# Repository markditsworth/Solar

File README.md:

# Solar

#### 300 Watt Solar Bank with Battery Storage

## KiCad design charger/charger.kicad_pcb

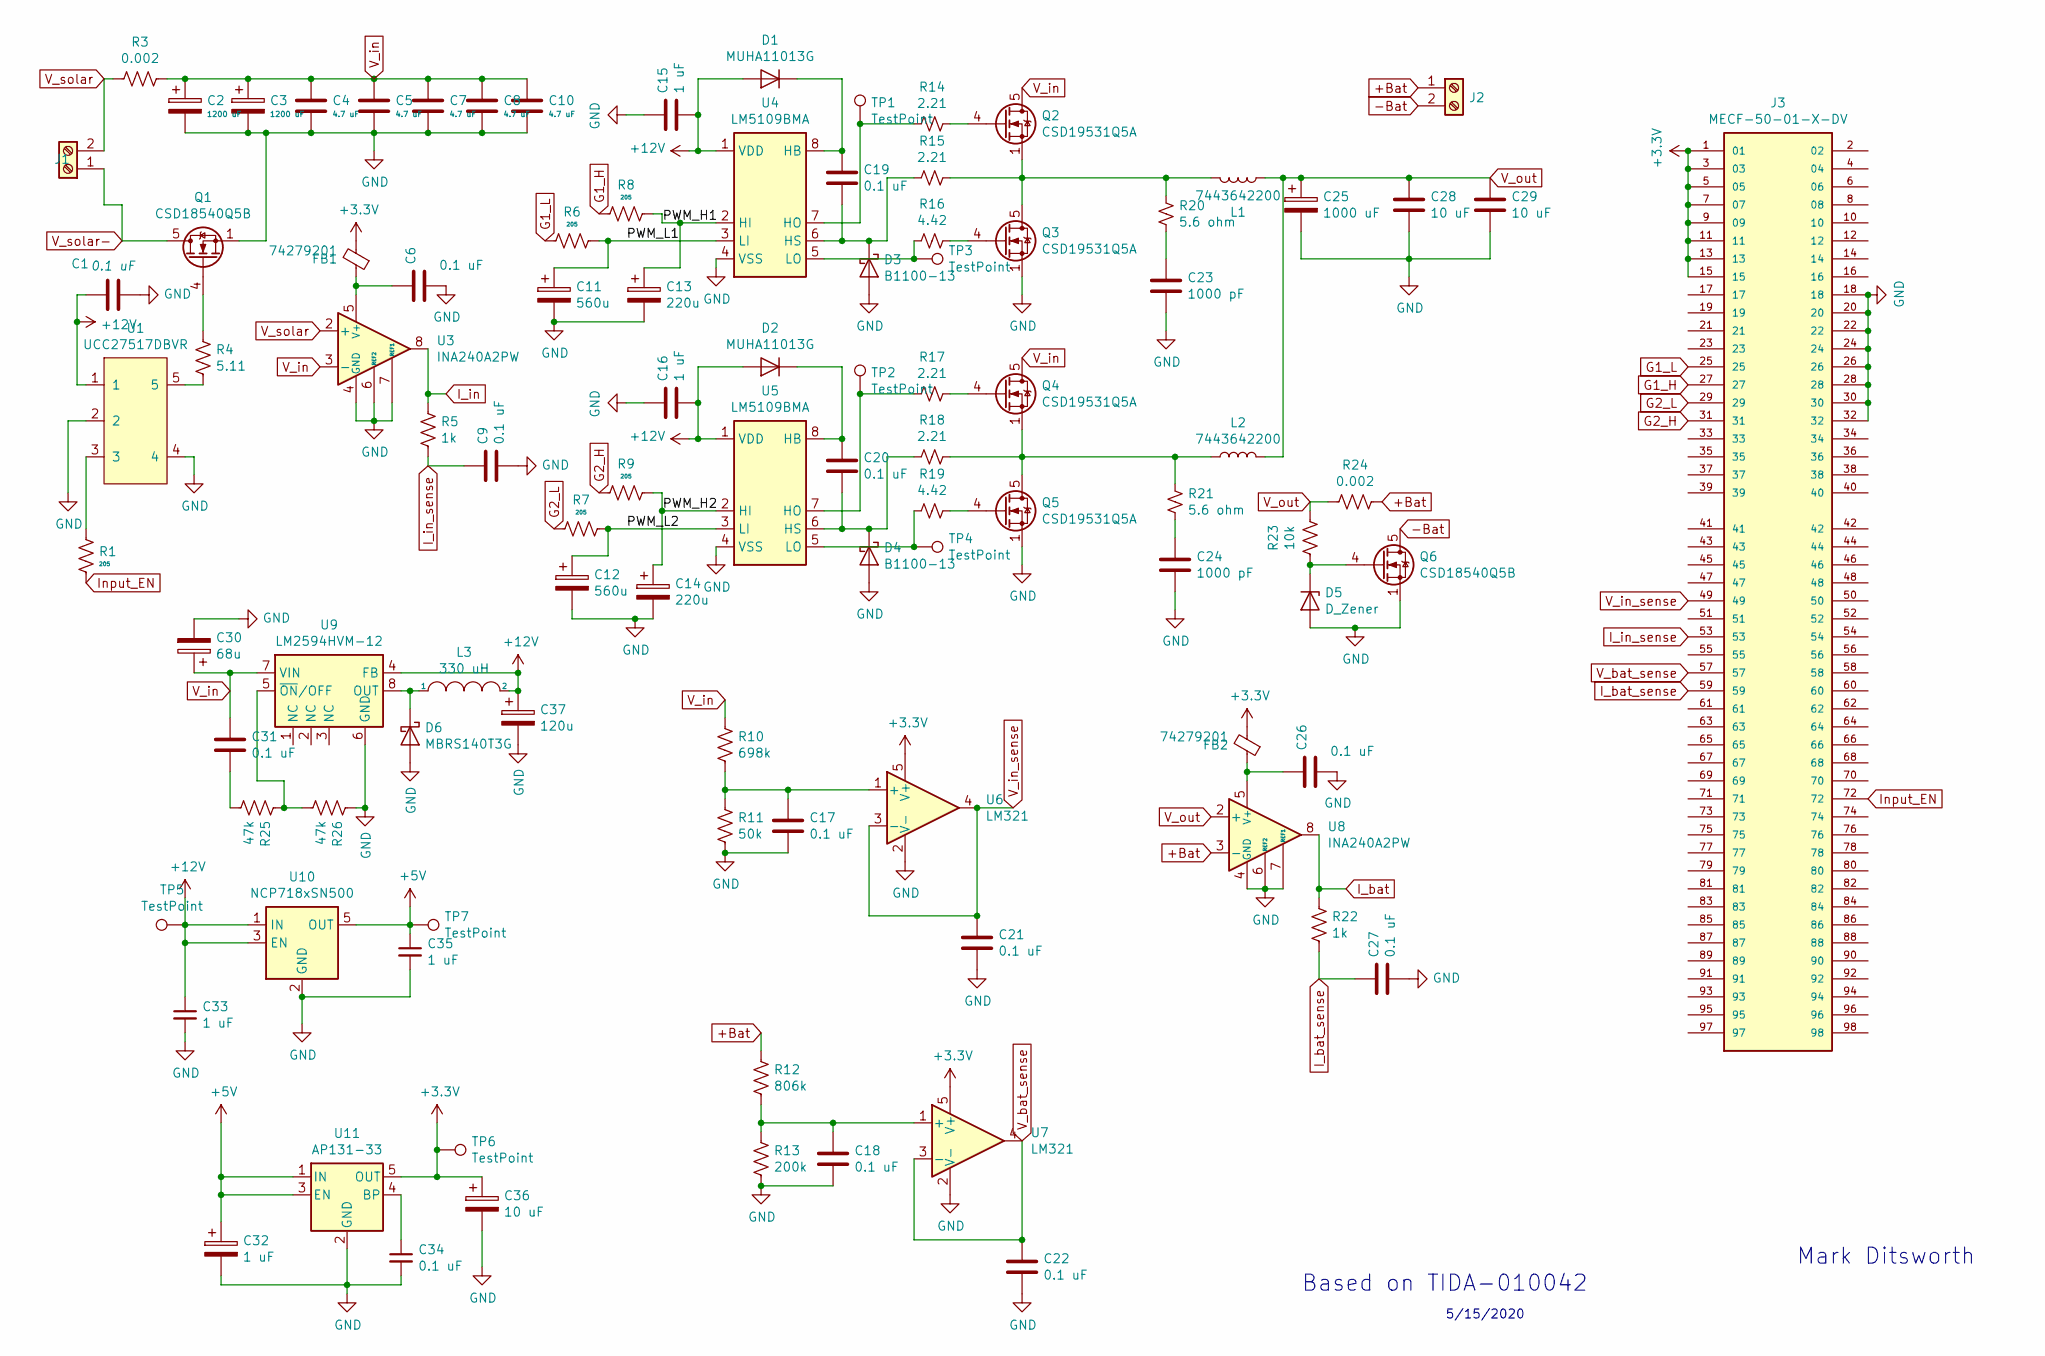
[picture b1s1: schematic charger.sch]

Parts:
C1, C6, C9, C17, C18, C19, C20, C21, C22, C26, C27, C31, C34: 0.1 uF; C_1206_3216Metric
C2, C3: 1200 uF; CP_Radial_D25.0mm_P10.00mm_SnapIn
C4, C5, C7, C8, C10: 4.7 uF; C_1206_3216Metric
C11, C12: 560u; C_Elec_8x10.2
C13, C14: 220u; C_Elec_6.3x7.7
C15, C16, C33, C35: 1 uF; C_1206_3216Metric
C23, C24: 1000 pF; C_1206_3216Metric
C25: 1000 uF; CP_Radial_D30.0mm_P10.00mm_SnapIn
C28, C29: 10 uF; C_1206_3216Metric
C30: 68u; C_Elec_8x10.2
C32: 1 uF; CP_Radial_D5.0mm_P2.00mm
C36: 10 uF; CP_Radial_D6.3mm_P2.50mm
C37: 120u; C_Elec_10x10.2
D1, D2: MUHA11013G; D_SMA
D3, D4: B1100-13; D_SMA
D5: D_Zener; D_SMA
D6: MBRS140T3G; D_SMB_Handsoldering
FB1, FB2: 74279201; L_0805_2012Metric
J1, J2: OSTT7020150; Phoenix_MKDS_6.35
J3: MECF-50-01-X-DV; SAMTEC_MECF-50-01-X-DV; PARTREV D
L1, L2: 7443642200; 7443642200 _Inductor
L3: 330 uH; L_Bourns_SRR1260
Q1, Q6: CSD18540Q5B; TDSON-8-1
Q2, Q3, Q4, Q5: CSD19531Q5A; TDSON-8-1
R1, R6, R7, R8, R9: 205; R_1206_3216Metric
R3, R24: 0.002; R_2512_6332Metric
R4: 5.11; R_1206_3216Metric
R5, R22: 1k; R_1206_3216Metric
R10: 698k; R_1206_3216Metric
R11: 50k; R_1206_3216Metric
R12: 806k; R_1206_3216Metric
R13: 200k; R_1206_3216Metric
R14, R15, R17, R18: 2.21; R_1206_3216Metric
R16, R19: 4.42; R_1206_3216Metric
R20, R21: 5.6 ohm; R_1206_3216Metric
R23: 10k; R_1206_3216Metric
R25, R26: 47k; R_1206_3216Metric
TP1, TP2, TP3, TP4, TP5, TP6, TP7: TestPoint; Pin_D1.4mm_L8.5mm_W2.8mm_FlatFork
U1: UCC27517DBVR; SOT-23-5
U3, U8: INA240A2PW; SOIC-8_3.9x4.9mm_P1.27mm
U4, U5: LM5109BMA; SOIC-8_3.9x4.9mm_P1.27mm
U6, U7: LM321; SOT-23-5
U9: LM2594HVM-12; SOIC-8_3.9x4.9mm_P1.27mm
U10: NCP718xSN500; SOT-23-5
U11: AP131-33; SOT-23-5

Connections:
+3V3: C36.1, FB1.2, FB2.2, J3.1, J3.3, J3.5, J3.7, J3.9, J3.11, J3.13, J3.15, TP6.1, U6.5 (V+), U7.5 (V+), U11.5 (OUT)
+5V: C32.1, C35.1, TP7.1, U10.5 (OUT), U11.1 (IN), U11.3 (EN)
+12V: C1.2, C15.2, C16.2, C33.1, C37.1, D1.2 (A), D2.2 (A), L3.2, TP5.1, U1.1, U4.1 (VDD), U5.1 (VDD), U9.4 (FB), U10.1 (IN), U10.3 (EN)
+Bat: J2.1, R12.1, R24.1, U8.3 (-)
-Bat: J2.2, Q6.5 (D)
/PWM_H1: C13.1, R8.1, U4.2 (HI)
/PWM_H2: C14.1, R9.1, U5.2 (HI)
/PWM_L1: C11.1, R6.1, U4.3 (LI)
/PWM_L2: C12.1, R7.1, U5.3 (LI)
G1_H: J3.27, R8.2
G1_L: J3.25, R6.2
G2_H: J3.31, R9.2
G2_L: J3.29, R7.2
GND: C1.1, C2.2, C3.2, C4.2, C5.2, C6.2, C7.2, C8.2, C9.2, C10.2, C11.2, C12.2, C13.2, C14.2, C15.1, C16.1, C17.2, C18.2, C21.2, C22.2, C23.2, C24.2, C25.2, C26.2, C27.2, C28.2, C29.2, C30.2, C32.2, C33.2, C34.2, C35.2, C36.2, C37.2, D3.2 (A), D4.2 (A), D5.2 (A), D6.2 (A), J3.18, J3.20, J3.22, J3.24, J3.26, J3.28, J3.30, J3.32, Q1.1 (S), Q1.2 (S), Q1.3 (S), Q3.1 (S), Q3.2 (S), Q3.3 (S), Q5.1 (S), Q5.2 (S), Q5.3 (S), Q6.1 (S), Q6.2 (S), Q6.3 (S), R11.2, R13.2, R26.1, U1.2, U1.4, U3.1 (GND), U3.4 (GND), U3.6 (REF2), U3.7 (REF1), U4.4 (VSS), U5.4 (VSS), U6.2 (V-), U7.2 (V-), U8.1 (GND), U8.4 (GND), U8.6 (REF2), U8.7 (REF1), U9.6 (GND), U10.2 (GND), U11.2 (GND)
I_bat: R22.1, U8.8
I_bat_sense: C27.1, J3.59, R22.2
I_in: R5.1, U3.8
I_in_sense: C9.1, J3.53, R5.2
Input_EN: J3.72, R1.1
unnamed: C6.1, FB1.1, U3.5 (V+)
unnamed: C17.1, R10.2, R11.1, U6.1 (+)
unnamed: C18.1, R12.2, R13.1, U7.1 (+)
unnamed: C19.1, D1.1 (K), U4.8 (HB)
unnamed: C19.2, D3.1 (K), R15.2, U4.6 (HS)
unnamed: C20.1, D2.1 (K), U5.8 (HB)
unnamed: C20.2, D4.1 (K), R18.2, U5.6 (HS)
unnamed: C23.1, R20.2
unnamed: C24.1, R21.2
unnamed: C26.1, FB2.1, U8.5 (V+)
unnamed: C31.2, R25.2
unnamed: C34.1, U11.4 (BP)
unnamed: D5.1 (K), Q6.4 (G), R23.2
unnamed: D6.1 (K), L3.1, U9.8 (OUT)
unnamed: L1.2, Q2.1 (S), Q2.2 (S), Q2.3 (S), Q3.5 (D), R15.1, R20.1
unnamed: L2.1, Q4.1 (S), Q4.2 (S), Q4.3 (S), Q5.5 (D), R18.1, R21.1
unnamed: Q1.4 (G), R4.1
unnamed: Q2.4 (G), R14.1
unnamed: Q3.4 (G), R16.1
unnamed: Q4.4 (G), R17.1
unnamed: Q5.4 (G), R19.1
unnamed: R1.2, U1.3
unnamed: R4.2, U1.5
unnamed: R14.2, TP1.1, U4.7 (HO)
unnamed: R16.2, TP3.1, U4.5 (LO)
unnamed: R17.2, TP2.1, U5.7 (HO)
unnamed: R19.2, TP4.1, U5.5 (LO)
unnamed: R25.1, R26.2, U9.5 (~ON~/OFF)
V_bat_sense: C22.1, J3.57, U7.3 (-), U7.4
V_in: C2.1, C3.1, C4.1, C5.1, C7.1, C8.1, C10.1, C30.1, C31.1, Q2.5 (D), Q4.5 (D), R3.1, R10.1, U3.3 (-), U9.7 (VIN)
V_in_sense: C21.1, J3.49, U6.3 (-), U6.4
V_out: C25.1, C28.1, C29.1, L1.1, L2.2, R23.1, R24.2, U8.2 (+)
V_solar: J1.2, R3.2, U3.2 (+)
V_solar-: J1.1, Q1.5 (D)

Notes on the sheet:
Mark Ditsworth
Based on TIDA-010042
5/15/2020

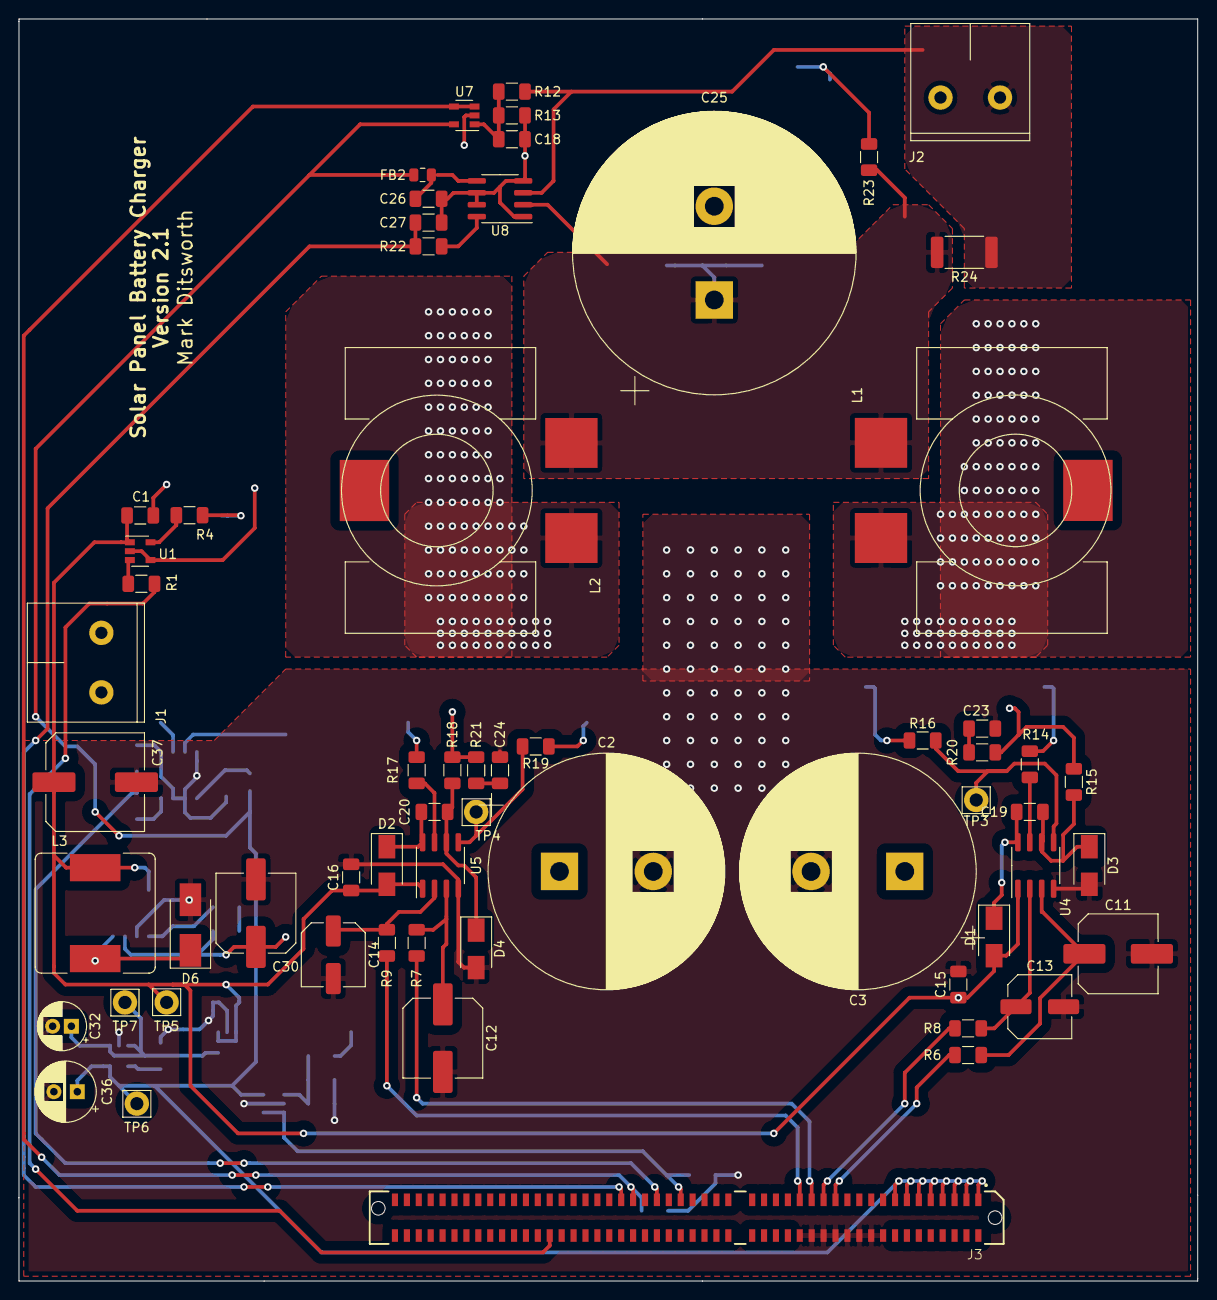
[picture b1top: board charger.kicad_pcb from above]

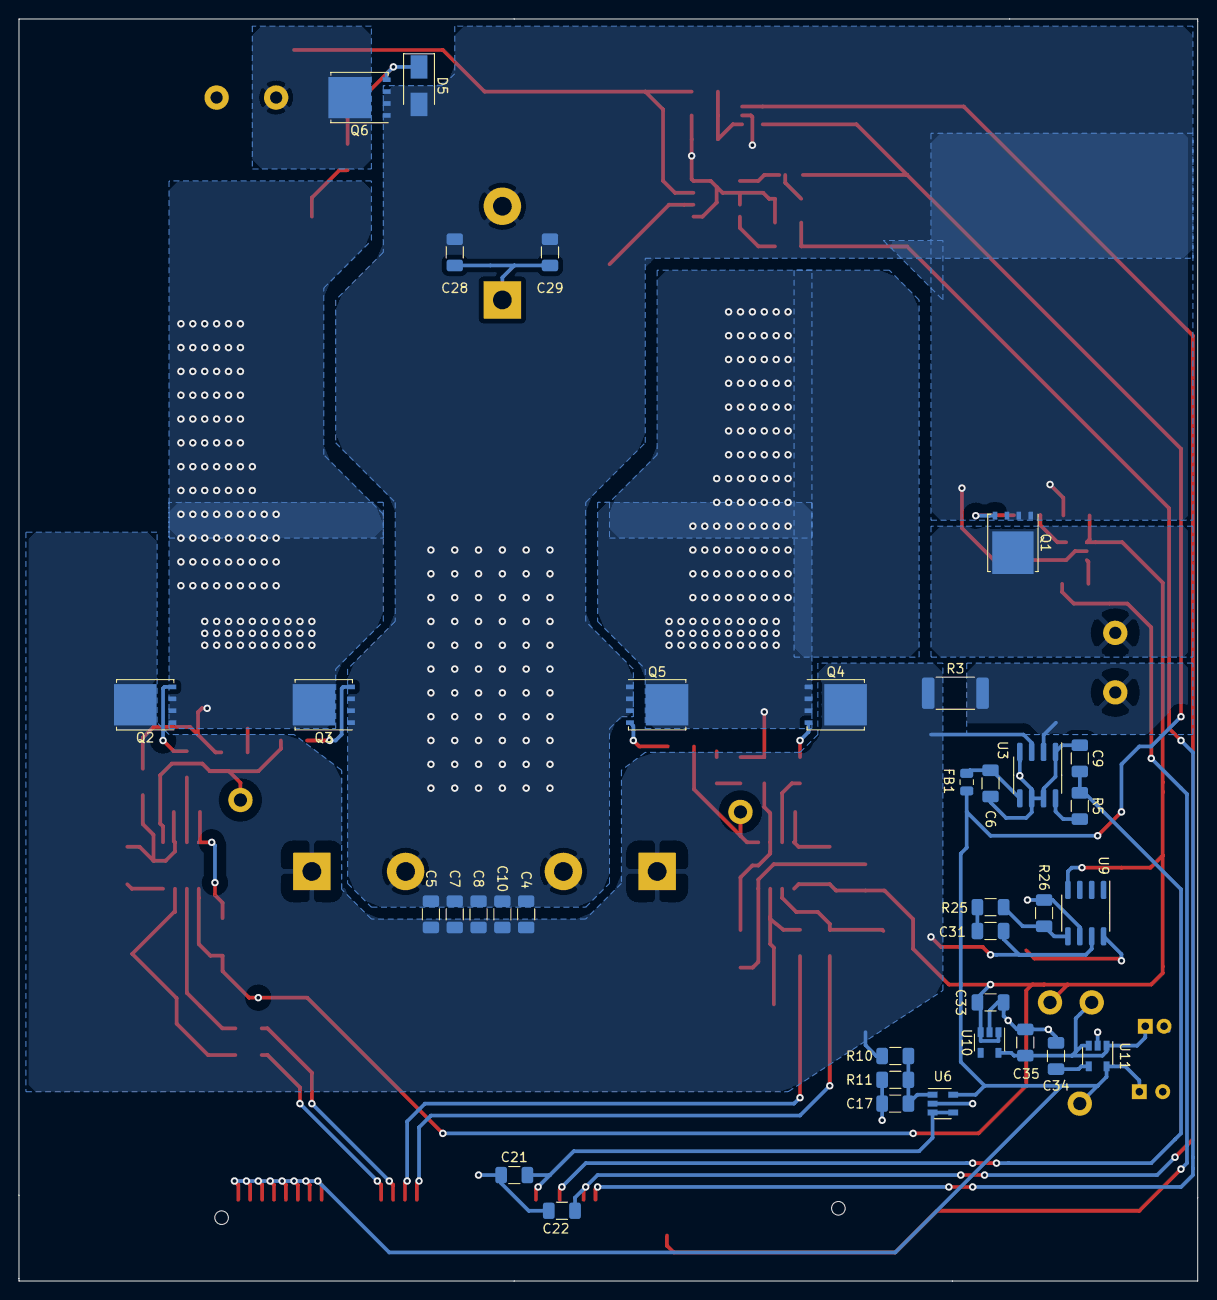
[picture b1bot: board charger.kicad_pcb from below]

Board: 2 copper layers, 125.7 x 134.6 mm, 97 parts (35 on the bottom side), 53 nets.

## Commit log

2020-05-12 add application doc
2020-05-12 add charger project
2020-05-12 added aux power schem
2020-05-13 add power circuit
2020-05-13 added connectors
2020-05-14 add ckt enable/disable
2020-05-15 add voltage dividers
2020-05-16 begin with footprints
2020-10-26 add footprints
2020-10-27 start on pcb
2020-10-28 finished pcb
2020-12-03 charger pcb v2
2020-12-05 add .gitignore
2020-12-05 update gitignore
2020-12-05 update printf
2020-12-05 add pinout diagram
2020-12-05 add startup file
2020-12-06 ADC + UART tx minimal function working
2020-12-07 ready for more testing
